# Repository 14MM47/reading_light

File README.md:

# Moon reading light

A clip-on book light: a slim pack clips to the back cover of a book, a ~12 cm plastic-sleeved metal gooseneck rises
from its top, and a 50 mm 3D-printed lithophane moon at the end glows from LEDs in its base. One slide switch turns
it on and off; a main button cycles ten light modes (CRI-97 tunable whites from 2700 K to 5000 K, 6500 K and a 1900 K candle mixed with the RGB LED, red/orange
night lights, green, blue); up/down buttons set brightness; holding the main button for 2 s saves the current
colour and brightness as the power-on default. USB-C charging, 1200 mAh LiPo.

This repo was produced end to end by Claude Code as a test of the full product-design process
(requirements → research → electronics → layout → firmware → mechanical → verification → BOM/ordering).

| What | Where |
|---|---|
| **Everything to build it, in build order** (PCB files, order lists, print files, firmware hex, drawings, PDFs of every instruction and checklist) | [`deliverable/`](deliverable/): start with `00-START-HERE.pdf` |
| How every part fits (exploded and section views) | [`docs/design/fitment/`](docs/design/fitment/) |
| Requirements, architecture, decisions, status | [`PLAN.md`](PLAN.md) |
| PCB fabrication files (Gerbers zip, BOM, pick-and-place, PDFs, STEP) | [`fab/`](fab/) |
| Printed parts, ready to slice (STL + 3MF) and print settings | [`print/`](print/) |
| Farnell order list and other purchases, assembly cost comparison | [`bom/`](bom/) |
| Firmware (PlatformIO) | [`firmware/`](firmware/) |
| KiCad projects and the generator | [`hardware/`](hardware/) |
| Part models (build123d) and the check pipeline | [`cad/`](cad/) |
| Design calculations, optics, thermal, verification reports | [`docs/`](docs/) |
| Step-by-step handoffs for Claude Code in VS Code (ordering, printing, flashing, bring-up) | [`docs/handoffs/`](docs/handoffs/) |

Moon texture: NASA's Scientific Visualization Studio, CGI Moon Kit (LRO LROC / LOLA data, public domain).

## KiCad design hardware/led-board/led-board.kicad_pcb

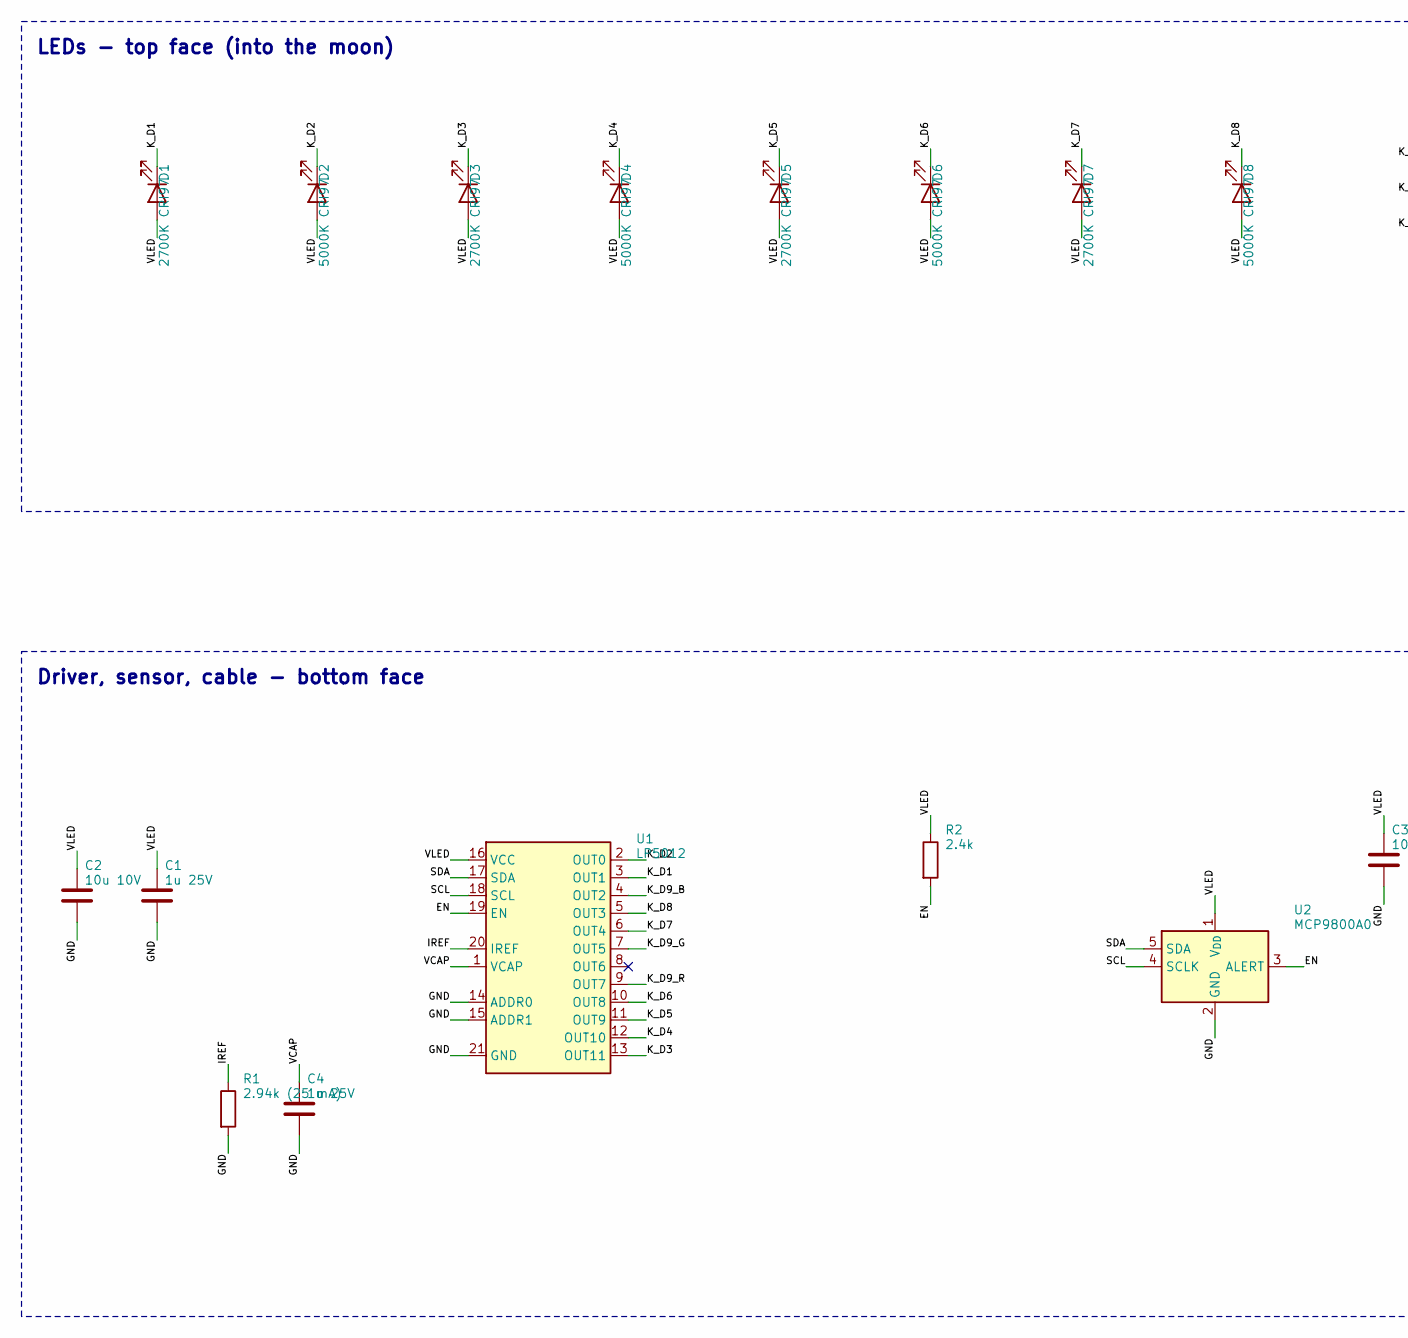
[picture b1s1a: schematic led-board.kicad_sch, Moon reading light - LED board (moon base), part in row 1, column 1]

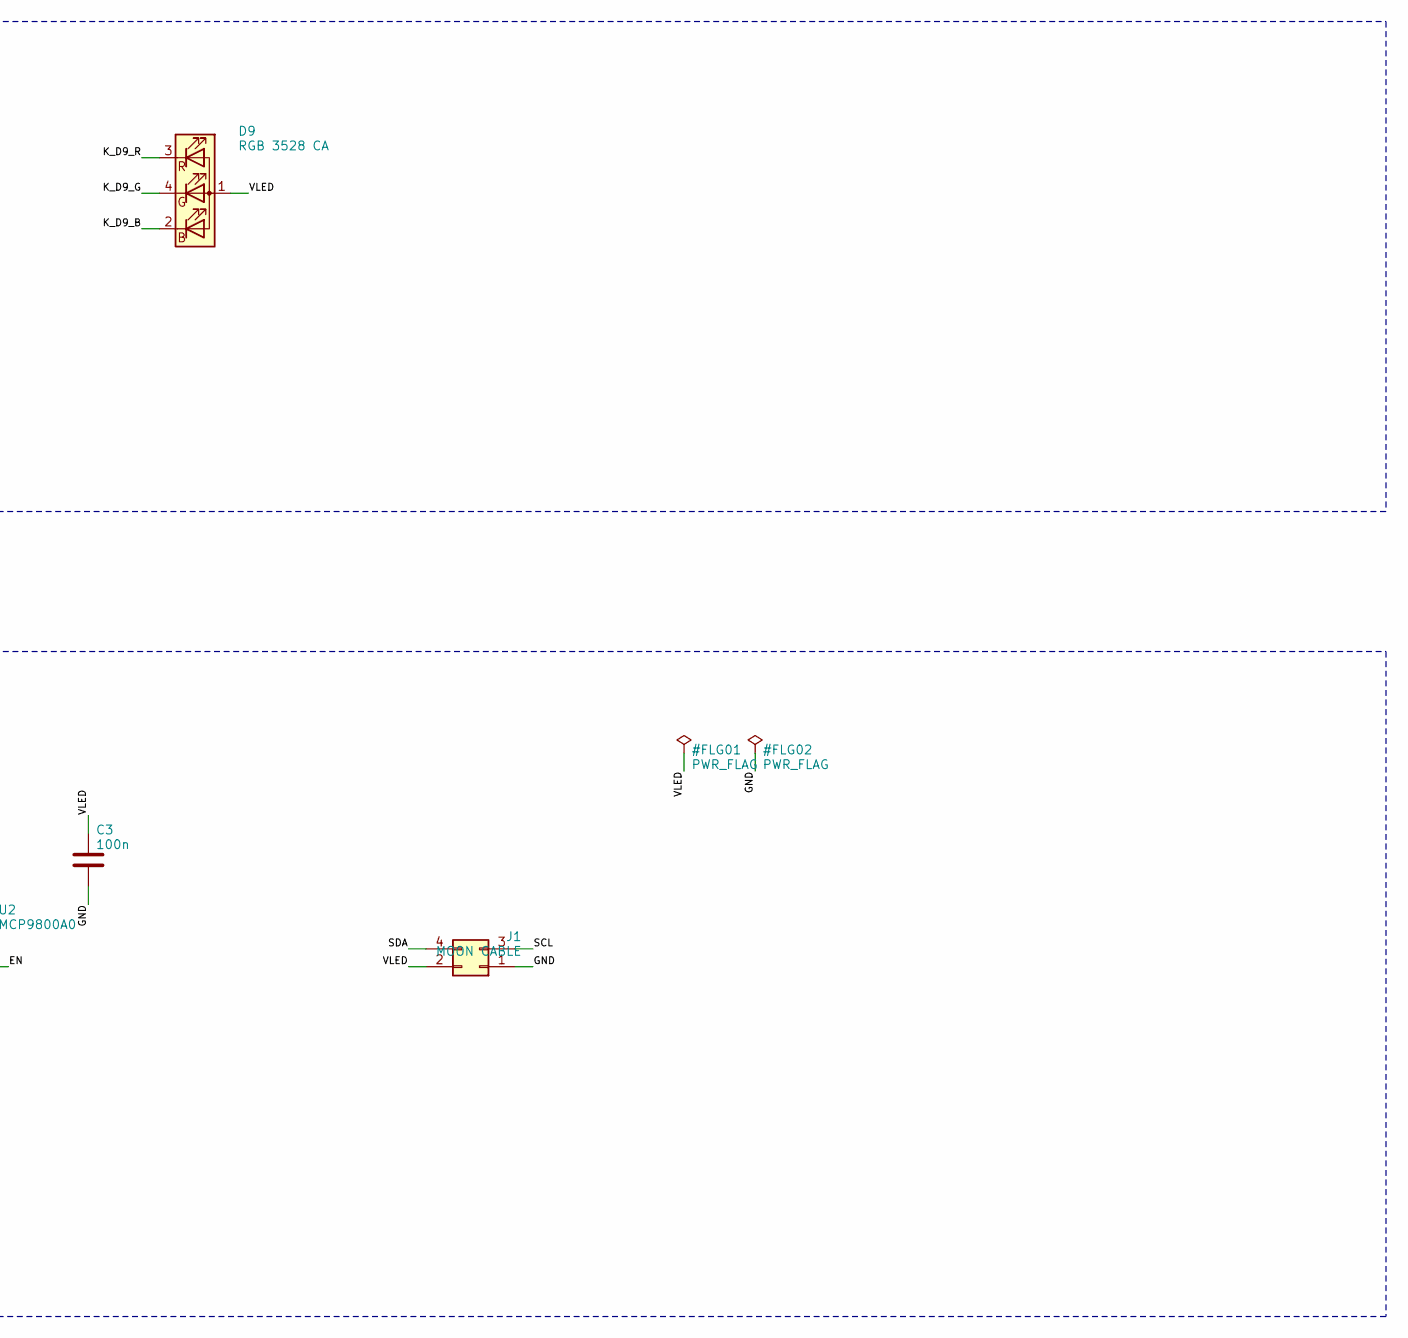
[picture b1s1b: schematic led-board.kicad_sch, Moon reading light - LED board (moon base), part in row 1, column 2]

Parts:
C1, C4: 1u 25V; C_0402_1005Metric; MPN GRM155R61E105KA12D
C2: 10u 10V; C_0603_1608Metric; MPN GRM188R61A106KE69D
C3: 100n; C_0402_1005Metric; MPN GRM155R71C104KA88D
D1, D3, D5, D7: 2700K CRI97; LED_PLCC_2835_Dense; MPN BXEN-27S-11M-3C-00-0-3; Farnell 3498849
D2, D4, D6, D8: 5000K CRI97; LED_PLCC_2835_Dense; MPN BXEN-50S-11M-3C-00-0-3; Farnell 3498853
D9: RGB 3528 CA; LED_RGB_Wuerth-PLCC4_3.2x2.8mm_150141M173100; MPN 150141M173100; Farnell 2322115
J1: MOON CABLE; LED_WirePads_2x02_P1.90mm
R1: 2.94k (25 mA); R_0402_1005Metric; MPN RC0402FR-072K94L
R2: 2.4k; R_0402_1005Metric; MPN RC0402FR-072K4L
U1: LP5012; Texas_RUK0020B_WQFN-20-1EP_3x3mm_P0.4mm_EP1.7x1.7mm; MPN LP5012RUKR
U2: MCP9800A0; SOT-23-5; MPN MCP9800A0T-M/OT; Farnell 1439485

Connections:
/EN: R2.2, U1.19 (EN), U2.3 (ALERT)
/GND: C1.2, C2.2, C3.2, C4.2, J1.1, R1.2, U1.14 (ADDR0), U1.15 (ADDR1), U1.21 (GND), U2.2 (GND)
/IREF: R1.1, U1.20 (IREF)
/K_D1: D1.1 (K), U1.3 (OUT1)
/K_D2: D2.1 (K), U1.2 (OUT0)
/K_D3: D3.1 (K), U1.13 (OUT11)
/K_D4: D4.1 (K), U1.12 (OUT10)
/K_D5: D5.1 (K), U1.11 (OUT9)
/K_D6: D6.1 (K), U1.10 (OUT8)
/K_D7: D7.1 (K), U1.6 (OUT4)
/K_D8: D8.1 (K), U1.5 (OUT3)
/K_D9_B: D9.2 (BK), U1.4 (OUT2)
/K_D9_G: D9.4 (GK), U1.7 (OUT5)
/K_D9_R: D9.3 (RK), U1.9 (OUT7)
/SCL: J1.3, U1.18 (SCL), U2.4 (SCLK)
/SDA: J1.4, U1.17 (SDA), U2.5 (SDA)
/VCAP: C4.1, U1.1 (VCAP)
/VLED: C1.1, C2.1, C3.1, D1.2 (A), D2.2 (A), D3.2 (A), D4.2 (A), D5.2 (A), D6.2 (A), D7.2 (A), D8.2 (A), D9.1 (A), J1.2, R2.1, U1.16 (VCC), U2.1 (V_{DD})

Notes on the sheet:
LEDs - top face (into the moon)
Driver, sensor, cable - bottom face

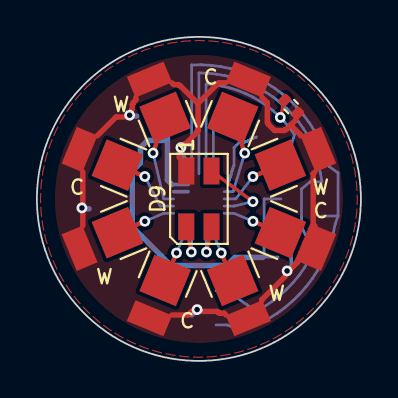
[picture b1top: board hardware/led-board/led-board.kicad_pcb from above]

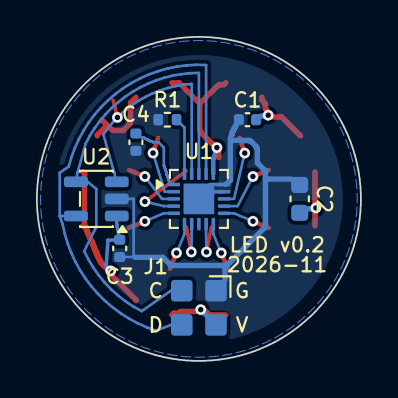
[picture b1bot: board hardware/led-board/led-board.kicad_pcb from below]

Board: 2 copper layers, 18.0 x 18.0 mm, 18 parts (8 on the bottom side), 18 nets.

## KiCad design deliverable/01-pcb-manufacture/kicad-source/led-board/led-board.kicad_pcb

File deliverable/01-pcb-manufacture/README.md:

# 01: PCB manufacture

Two boards: main board rev 0.1, LED board rev 0.2. For each board, upload
**`<board>-v<rev>-gerbers.zip`** to the fab and copy the specs from **`FAB_NOTES.pdf`** (or `.md`) into the order
form. Instructions: `handoff-01-pcb-order.pdf`.

| Board | Size | Stack | Finish / mask | Stencil | Qty |
|---|---|---|---|---|---|
| `main-board/` (in the pack) | 35 × 62 mm | 2 layers, 1.6 mm FR4, 1 oz | HASL lead-free, green / white silk | top, 0.12 mm | 5 |
| `led-board/` (in the moon base) | **Ø 18 mm** round, 0.15/0.15 mm rules | 2 layers, **1.0 mm** FR4, 1 oz | **ENIG, white mask / black silk** | top 0.12 mm **and** bottom **0.10 mm** | 5 |

Files per board:
- `*-gerbers.zip`: Gerber X2 for every layer, plus PTH and NPTH Excellon drill files. **This is the upload.**
- `FAB_NOTES.*`: board spec, special requests, what the remaining DRC warnings mean.
- `*-schematic.pdf`, `*.step`: some fabs ask for these. The STEP lacks 3D models for J1, J2, F1 and the 2835 LEDs;
  re-export it locally before using it for fit checks.
- `optional-assembly-service/`: BOM and placement files for PCBWay or JLCPCB, **only if you choose fab assembly**.
  Main board: bare board plus hand assembly. LED board: fab assembly of the bottom face (U1, U2, R1, C1–C4) is
  recommended, then hand-fit the top (`02-parts-order/assembly-routes-cost-comparison.pdf`).
- `images/`: top and bottom renders for a visual check against the fab's online viewer.

`kicad-source/`: the generated KiCad 9 projects with their project symbol and footprint library, so the
`../lib` paths resolve. PCBWay can take a `.kicad_pcb` directly. These are generated from `hardware/<board>/design.py`;
edit the Python, not these files.

Check results: main-board ERC 0, DRC errors 0,
unconnected 0; led-board ERC 0, DRC errors
0, unconnected 0.

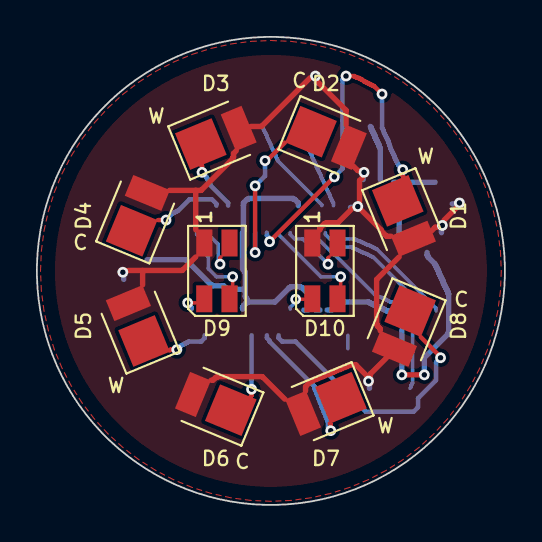
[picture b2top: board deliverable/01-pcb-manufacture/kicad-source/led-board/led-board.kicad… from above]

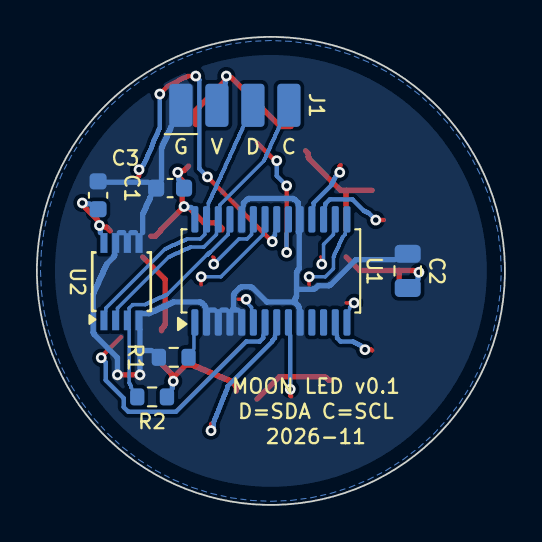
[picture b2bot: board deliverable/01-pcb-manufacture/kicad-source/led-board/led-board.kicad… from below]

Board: 2 copper layers, 26.0 x 26.0 mm, 18 parts (8 on the bottom side), 20 nets.

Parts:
C1, C3: 100n; C_0603_1608Metric
C2: 10u 16V 0805; C_0805_2012Metric
D1, D3, D5, D7: 2700K CRI97; LED_PLCC_2835
D2, D4, D6, D8: 5000K CRI97; LED_PLCC_2835
D9, D10: RGB 3528 CA; LED_RGB_Wuerth-PLCC4_3.2x2.8mm_150141M173100
J1: MOON CABLE; LED_WirePads_1x04_P2.00mm
R1: 750 (25 mA); R_0603_1608Metric
R2: 2.4k; R_0603_1608Metric
U1: TLC59116IPWR; TSSOP-28_4.4x9.7mm_P0.65mm
U2: LM75BDP; TSSOP-8_3x3mm_P0.65mm

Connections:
/GND: C1.2, C2.2, C3.2, J1.1, R1.2, U1.2, U1.3, U1.4, U1.5, U1.10, U1.19, U1.24, U2.4, U2.5, U2.6, U2.7
/K_D1: D1.1, U1.21
/K_D2: D2.1, U1.20
/K_D3: D3.1, U1.18
/K_D4: D4.1, U1.17
/K_D5: D5.1, U1.13
/K_D6: D6.1, U1.9
/K_D7: D7.1, U1.8
/K_D8: D8.1, U1.7
/K_D9_B: D9.2, U1.16
/K_D9_G: D9.4, U1.15
/K_D9_R: D9.3, U1.14
/K_D10_B: D10.2, U1.23
/K_D10_G: D10.4, U1.22
/K_D10_R: D10.3, U1.6
/RESET_N: R2.2, U1.25, U2.3
/REXT: R1.1, U1.1
/SCL: J1.4, U1.26, U2.2
/SDA: J1.3, U1.27, U2.1
/VLED: C1.1, C2.1, C3.1, D1.2, D2.2, D3.2, D4.2, D5.2, D6.2, D7.2, D8.2, D9.1, D10.1, J1.2, R2.1, U1.28, U2.8

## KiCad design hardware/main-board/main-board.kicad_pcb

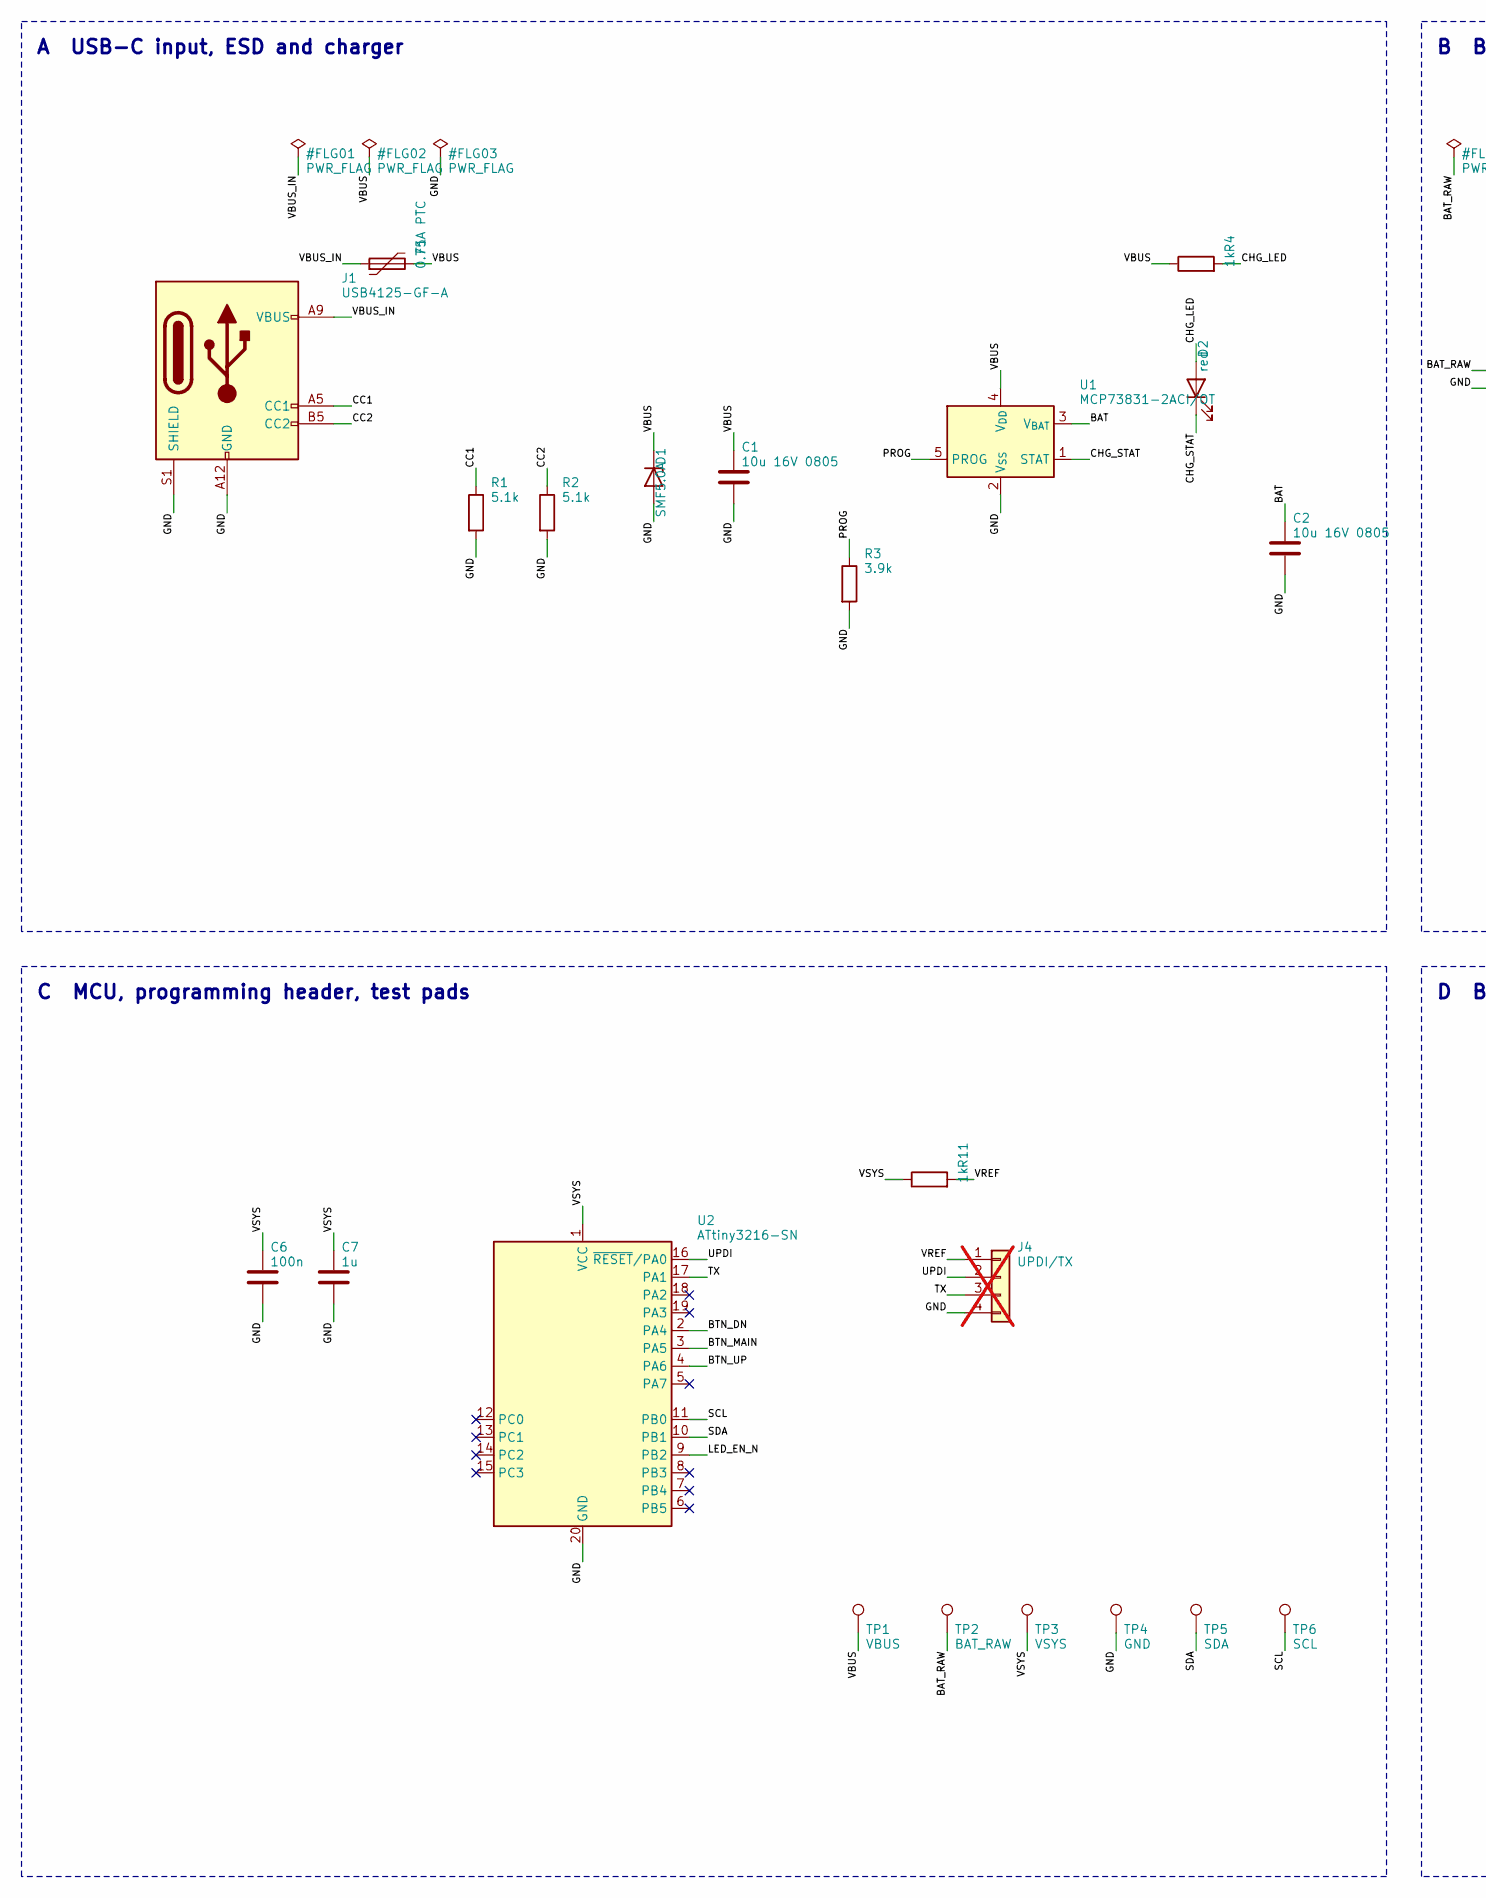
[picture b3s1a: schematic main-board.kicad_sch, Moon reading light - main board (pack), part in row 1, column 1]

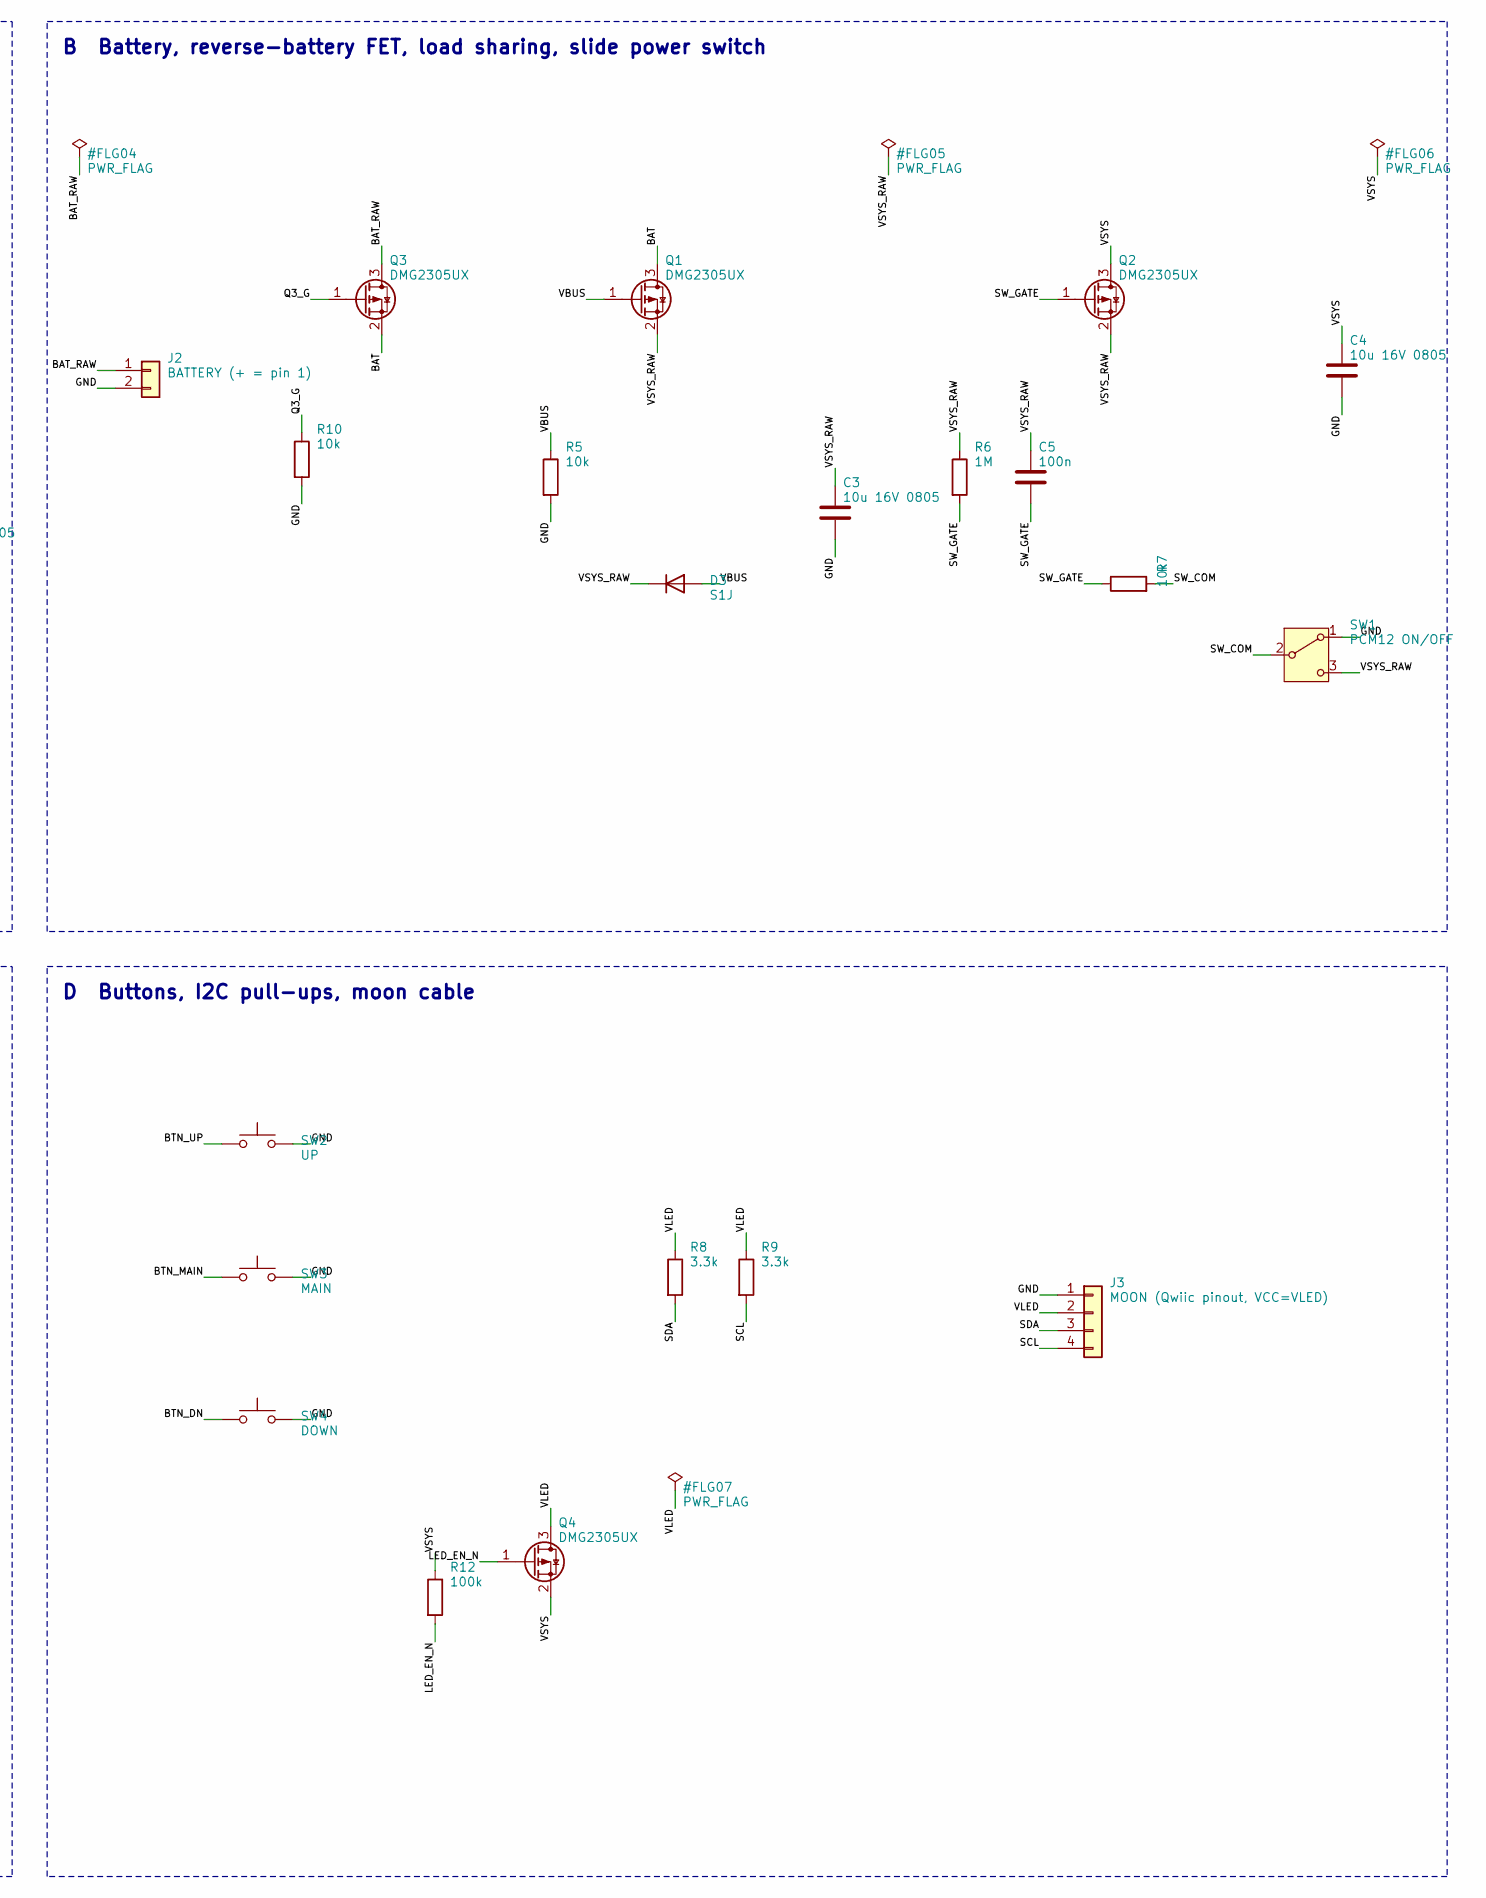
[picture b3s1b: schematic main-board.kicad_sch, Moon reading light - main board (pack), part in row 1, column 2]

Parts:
C1, C2, C3, C4: 10u 16V 0805; C_0805_2012Metric; MPN CL21A106KOQNNNE
C5, C6: 100n; C_0603_1608Metric; MPN MC0603B104K500CT; Farnell 1759122
C7: 1u; C_0603_1608Metric; MPN CL10A105KB8NNNC; Farnell 3013385
D1: SMF5.0A; D_SOD-123F; MPN SMF5.0A; Farnell 2691565
D2: red; LED_0603_1608Metric; MPN APT1608SURCK
D3: S1J; D_SMA; MPN S1J-E3/61T
F1: 0.75A PTC; Fuse_1812_4532Metric; MPN MF-MSMF075-2
J1: USB4125-GF-A; USB_C_Receptacle_GCT_USB4125-xx-x_6P_TopMnt_Horizontal; MPN USB4125-GF-A; Farnell 3648642
J2: BATTERY (+ = pin 1); JST_PH_S2B-PH-SM4-TB_1x02-1MP_P2.00mm_Horizontal; MPN S2B-PH-SM4-TB(LF)(SN); Farnell 9492615
J3: MOON (Qwiic pinout, VCC=VLED); JST_SH_SM04B-SRSS-TB_1x04-1MP_P1.00mm_Horizontal; MPN SM04B-SRSS-TB(LF)(SN); Farnell 1830839
J4: UPDI/TX; PinHeader_1x04_P2.54mm_Vertical; MPN DNP; not fitted
Q1, Q2, Q3, Q4: DMG2305UX; SOT-23; MPN DMG2305UX-7; Farnell 2543533
R1, R2: 5.1k; R_0603_1608Metric; MPN MCWR06X5101FTL
R3: 3.9k; R_0603_1608Metric; MPN MCWR06X3901FTL
R4, R11: 1k; R_0603_1608Metric; MPN MCWR06X1001FTL
R5, R7, R10: 10k; R_0603_1608Metric; MPN MCWR06X1002FTL; Farnell 2447230
R6: 1M; R_0603_1608Metric; MPN MCWR06X1004FTL
R8, R9: 3.3k; R_0603_1608Metric; MPN MCWR06X3301FTL
R12: 100k; R_0603_1608Metric; MPN MCWR06X1003FTL
SW1: PCM12 ON/OFF; SW_SPDT_PCM12; MPN PCM12SMTR; Farnell 9575146
SW2: UP; SW_SPST_PTS645Sx43SMTR92; MPN PTS645SM43SMTR92 LFS; Farnell 3941596
SW3: MAIN; SW_SPST_PTS645Sx43SMTR92; MPN PTS645SM43SMTR92 LFS; Farnell 3941596
SW4: DOWN; SW_SPST_PTS645Sx43SMTR92; MPN PTS645SM43SMTR92 LFS; Farnell 3941596
TP1: VBUS; TestPoint_Pad_D1.5mm
TP2: BAT_RAW; TestPoint_Pad_D1.5mm
TP3: VSYS; TestPoint_Pad_D1.5mm
TP4: GND; TestPoint_Pad_D1.5mm
TP5: SDA; TestPoint_Pad_D1.5mm
TP6: SCL; TestPoint_Pad_D1.5mm
U1: MCP73831-2ACI/OT; SOT-23-5; MPN MCP73831T-2ACI/OT; Farnell 1332158
U2: ATtiny3216-SN; SOIC-20W_7.5x12.8mm_P1.27mm; MPN ATTINY3216-SN; Farnell 3018703

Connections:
/BAT: C2.1, Q1.3 (D), Q3.2 (S), U1.3 (V_{BAT})
/BAT_RAW: J2.1, Q3.3 (D), TP2.1
/BTN_DN: SW4.1, U2.2 (PA4)
/BTN_MAIN: SW3.1, U2.3 (PA5)
/BTN_UP: SW2.1, U2.4 (PA6)
/CC1: J1.A5 (CC1), R1.1
/CC2: J1.B5 (CC2), R2.1
/CHG_LED: D2.2 (A), R4.2
/CHG_STAT: D2.1 (K), U1.1 (STAT)
/GND: C1.2, C2.2, C3.2, C4.2, C6.2, C7.2, D1.2 (A), J1.A12 (GND), J1.B12 (GND), J1.S1 (SHIELD), J2.2, J3.1, J4.4, R1.2, R2.2, R3.2, R5.2, R10.2, SW1.1 (A), SW2.2, SW3.2, SW4.2, TP4.1, U1.2 (V_{SS}), U2.20 (GND)
/LED_EN_N: Q4.1 (G), R12.2, U2.9 (PB2)
/PROG: R3.1, U1.5 (PROG)
/Q3_G: Q3.1 (G), R10.1
/SCL: J3.4, R9.2, TP6.1, U2.11 (PB0)
/SDA: J3.3, R8.2, TP5.1, U2.10 (PB1)
/SW_COM: R7.2, SW1.2 (B)
/SW_GATE: C5.2, Q2.1 (G), R6.2, R7.1
/TX: J4.3, U2.17 (PA1)
/UPDI: J4.2, U2.16 (~RESET/PA0)
/VBUS: C1.1, D1.1 (K), D3.2 (A), F1.2, Q1.1 (G), R4.1, R5.1, TP1.1, U1.4 (V_{DD})
/VBUS_IN: F1.1, J1.A9 (VBUS), J1.B9 (VBUS)
/VLED: J3.2, Q4.3 (D), R8.1, R9.1
/VREF: J4.1, R11.2
/VSYS: C4.1, C6.1, C7.1, Q2.3 (D), Q4.2 (S), R11.1, R12.1, TP3.1, U2.1 (VCC)
/VSYS_RAW: C3.1, C5.1, D3.1 (K), Q1.2 (S), Q2.2 (S), R6.1, SW1.3 (C)

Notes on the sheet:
A USB-C input, ESD and charger
B Battery, reverse-battery FET, load sharing, slide power switch
C MCU, programming header, test pads
D Buttons, I2C pull-ups, moon cable

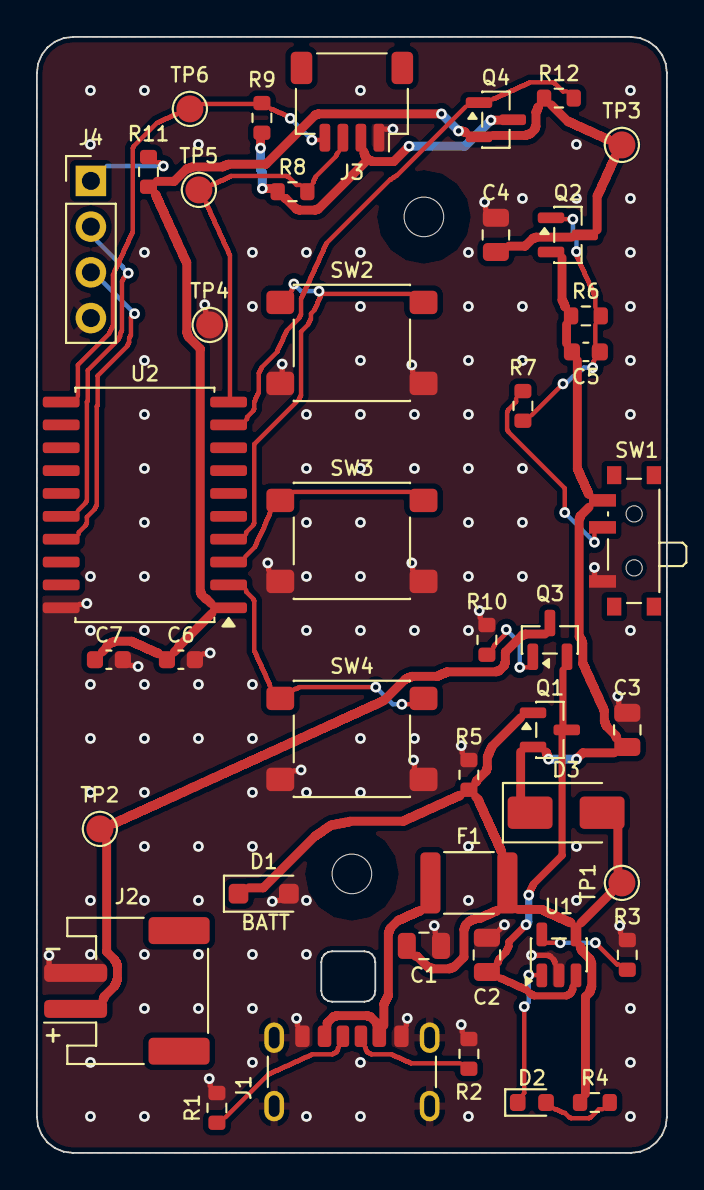
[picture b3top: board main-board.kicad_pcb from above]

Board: 2 copper layers, 35.0 x 62.0 mm, 45 parts (0 on the bottom side), 25 nets.

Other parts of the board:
H1, H2: hole

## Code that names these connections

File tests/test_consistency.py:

"""Cross-domain consistency: firmware <-> netlists <-> design files. Run: python3 -m pytest tests -q
(needs KiCad 9's kicad-cli on PATH and the generated hardware/*/reports/*.net from hardware/build.py)."""
import importlib.util
import re
import subprocess
from pathlib import Path

import pytest

ROOT = Path(__file__).resolve().parents[1]
GROUPS = {"WW": 0, "CW": 1, "R": 2, "G": 3, "B": 4}


def netlist(board):
    path = ROOT / "hardware" / board / "reports" / f"{board}.test.net"
    subprocess.run(["kicad-cli", "sch", "export", "netlist", "--format", "kicadsexpr", "-o", str(path),
                    str(ROOT / "hardware" / board / f"{board}.kicad_sch")], check=True, capture_output=True)
    text = path.read_text()
    path.unlink()
    nets = {}
    for m in re.finditer(r'\(net \(code "\d+"\) \(name "([^"]+)"\)(.*?)\)\s*\)\s*(?=\(net |\)\s*\)\s*$)', text, re.S):
        nodes = re.findall(r'\(node \(ref "([^"]+)"\) \(pin "([^"]+)"\)', m.group(2))
        nets[m.group(1)] = nodes
    return nets


def load_design(board):
    spec = importlib.util.spec_from_file_location(f"{board}_d", ROOT / "hardware" / board / "design.py")
    mod = importlib.util.module_from_spec(spec)
    spec.loader.exec_module(mod)
    return mod


def board_map():
    txt = (ROOT / "firmware" / "include" / "board_map.h").read_text()
    return [int(x) for x in re.search(r"OUT_GROUP\[N_OUT\] = \{([^}]*)\}", txt).group(1).split(",")]


def test_board_map_matches_led_netlist():
    d = load_design("led-board")
    nets = netlist("led-board")
    led_group = {ref: grp for ref, grp, _ in d.WHITE}
    rgb_pin = {"3": "R", "4": "G", "2": "B"}            # Device:LED_ABRG / Wurth 150141M173100
    rgb_refs = {d.RGB_REF}
    expect = [-1] * d.N_OUT
    for out, pin in d.PIN_OF_OUT.items():
        for name, nodes in nets.items():
            if ("U1", pin) in nodes:
                others = [(r, p) for r, p in nodes if r != "U1"]
                for r, p in others:
                    if r in led_group and p == "1":
                        expect[out] = GROUPS[led_group[r]]
                    elif r in rgb_refs and p in rgb_pin:
                        expect[out] = GROUPS[rgb_pin[p]]
    assert board_map() == expect


def test_firmware_pins_match_main_board():
    d = load_design("main-board")
    mcu = next(p for p in d.parts() if p.ref == "U2").pins
    cfg = (ROOT / "firmware" / "include" / "config.h").read_text()
    soic = {"PA4": "2", "PA5": "3", "PA6": "4", "PB2": "9", "PB0": "11", "PB1": "10", "PA1": "17", "PA0": "16"}
    for macro, net in (("PIN_BTN_UP", "BTN_UP"), ("PIN_BTN_MAIN", "BTN_MAIN"), ("PIN_BTN_DN", "BTN_DN"),
                       ("PIN_LED_EN_N", "LED_EN_N")):
        port = re.search(rf"#define {macro}\s+PIN_(P[ABC]\d)", cfg).group(1)
        assert mcu[soic[port]] == net, (macro, port)
    assert mcu["11"] == "SCL" and mcu["10"] == "SDA" and mcu["16"] == "UPDI" and mcu["17"] == "TX"


def test_channel_current_constant_matches_riref():
    d = load_design("led-board")
    riref = next(p for p in d.parts() if p.ref == "R1")
    assert riref.pins["1"] == "IREF"
    v = riref.value.split()[0]
    ohms = float(v[:-1]) * 1000 if v.endswith("k") else float(v)
    i_ma = 105 * 0.7 / ohms * 1000                         # LP5012: ISET = KIREF x VIREF / RIREF (SLVSEH2B)
    core = (ROOT / "firmware" / "lib" / "core" / "lightcore.h").read_text()
    fw = float(re.search(r"#define I_CHANNEL_MA\s+([\d.]+)f", core).group(1))
    assert abs(fw - i_ma) < 0.2, (fw, i_ma)


def test_group_led_counts_match_firmware():
    d = load_design("led-board")
    core = (ROOT / "firmware" / "lib" / "core" / "lightcore.cpp").read_text()
    counts = [int(x) for x in re.search(r"GROUP_LEDS\[G_COUNT\] = \{([^}]*)\}", core).group(1).split(",")]
    ww = sum(1 for w in d.WHITE if w[1] == "WW")
    cw = sum(1 for w in d.WHITE if w[1] == "CW")
    assert counts == [ww, cw, 1, 1, 1]                     # one RGB LED (D9) on LED board v0.2

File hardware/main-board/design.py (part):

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        P("C4", "C_10U", {"1": "VSYS", "2": "GND"}, (395, 70, 0)),
    ]
    # ---- C: MCU, programming header, test points (sheet bottom-left)
    # pins chosen for the layout: PA6/PA5/PA4 run top-to-bottom beside the UP/MAIN/DOWN buttons;
    # debug TX uses USART0's alternate pin PA1 (PORTMUX), next to UPDI and the header
    mcu = {"1": "VSYS", "20": "GND", "16": "UPDI", "17": "TX", "18": None, "19": None,
           "2": "BTN_DN", "3": "BTN_MAIN", "4": "BTN_UP", "5": None,
           "11": "SCL", "10": "SDA", "9": "LED_EN_N", "8": None, "7": None, "6": None,
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        P("C6", "C_100N", {"1": "VSYS", "2": "GND"}, (45, 200, 0)),
        P("C7", "C_1U", {"1": "VSYS", "2": "GND"}, (55, 200, 0)),
        P("R11", "R_1K", {"1": "VSYS", "2": "VREF"}, (140, 185, 90)),
        Part("J4", "Connector_Generic:Conn_01x04", "UPDI/TX", "Connector_PinHeader_2.54mm:PinHeader_1x04_P2.54mm_Vertical",
             {"1": "VREF", "2": "UPDI", "3": "TX", "4": "GND"}, sch=(150, 200, 0),
             fields={"Description": "Programming header: 1 VREF (sense only, 1k - never power the board here), 2 UPDI, 3 TX, 4 GND",
                     "MPN": "DNP", "Farnell": ""}, in_bom=False, dnp=True),
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        P("SW2", "TACT", {"1": "BTN_UP", "2": "GND"}, (240, 180, 0), value="UP"),
        P("SW3", "TACT", {"1": "BTN_MAIN", "2": "GND"}, (240, 200, 0), value="MAIN"),
        P("SW4", "TACT", {"1": "BTN_DN", "2": "GND"}, (240, 220, 0), value="DOWN"),
        # LED-board supply switch: the MCU (PB2 low) powers the LED board; off at reset (R12) and when the battery
        # is empty, so a flat cell is not drained by the LED board (LP5012 ~5 mA; v0.1 TLC59116 ~25 mA, review M2).
        # Pull-ups sit on the switched rail so the unpowered LED board is never back-fed through SDA/SCL.
        P("Q4", "PFET", {"1": "Q4_G", "2": "VSYS", "3": "VLED"}, (280, 240, 0), value="DMG2305UX"),
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        P("R8", "R_3K3", {"1": "VLED", "2": "SDA"}, (300, 200, 0)),
        P("R9", "R_3K3", {"1": "VLED", "2": "SCL"}, (310, 200, 0)),
        P("J3", "JST_SH4", {"1": "GND", "2": "VLED", "3": "SDA", "4": "SCL"}, (360, 205, 0),
          value="MOON (Qwiic pinout, VCC=VLED)"),
    ]
    return v

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BOXES = [(10, 20, 205, 150), (210, 20, 410, 150), (10, 155, 205, 285), (210, 155, 410, 285)]
COMMENTS = [
    "Charge 256 mA (R3 3.9k; total USB draw <= ~0.55 A: use a >= 1 A USB-C charger). Slide switch is the only on/off (Matt).",
    "J3 carries VLED (switched VSYS, not 3.3 V) on the Qwiic pinout: never plug a 3.3 V-only Qwiic device into it.",
    "J2 polarity: + on pin 1 (silk). Q3 blocks a reversed battery; meter every pack before plugging in.",
]

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    "R6": (30.5, 15.5, 0, "F"), "C5": (30.5, 17.5, 0, "F"), "R7": (27.0, 20.5, 90, "F"),
    "SW2": (17.5, 17.0, 0, "F"), "SW3": (17.5, 28.0, 0, "F"), "SW4": (17.5, 39.0, 0, "F"),
    "SW1": (32.85, 28.0, 90, "F"),          # slide switch, knob out of the right edge
    "U2": (6.0, 26.0, 180, "F"),            # pin 1 bottom-right: PA4-6 (buttons) face the buttons, PB0/1 (I2C) at the top
    "C6": (8.0, 34.6, 0, "F"), "C7": (4.0, 34.6, 0, "F"),
    "J4": (3.0, 8.0, 0, "F"),               # UPDI header, top-left (pins run down the left edge)
    "Q3": (28.5, 33.5, 90, "F"), "R10": (25.0, 33.5, 90, "F"),
    "Q1": (28.5, 38.5, 0, "F"), "C3": (32.8, 38.5, 90, "F"),
    "R5": (24.0, 41.0, 90, "F"), "D3": (29.4, 43.1, 0, "F"),
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
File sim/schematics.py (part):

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    d += e.Resistor().at((0, 0)).to((1.8, 0)).label("Rint 0.2 Ω", loc="bottom", fontsize=9)
    d += e.Inductor2(loops=2).at((1.8, 0)).to((3.4, 0)).label("lead 150 nH", loc="bottom", fontsize=9)
    d += e.Line().at((3.4, 0)).to((4.0, 0))
    d += e.Dot().at((4.0, 0)).label("BAT_RAW", loc="top", fontsize=8)
    s3, d3, g3 = _fet(d, 4.0, 0, src_left=False, gate_up=False, label="Q3")
    d += e.Line().at(g3).to((g3[0], -1.2))
    d += e.Resistor().at((g3[0], -1.2)).to((g3[0], -3.0)).label("R10 10k", loc="bottom", fontsize=9)
    d += e.Ground().at((g3[0], -3.0))
    d += e.Line().at(s3).to((6.6, 0))
    d += e.Dot().at((6.17, 0)).label("BAT", loc="bottom", fontsize=8)
    s1, d1, g1 = _fet(d, 6.6, 0, src_left=False, gate_up=True, label="Q1")
    d += e.Line().at(s1).to((9.8, 0))
    d += e.Dot().at((9.0, 0))
    d += e.Label().at((8.7, -0.45)).label("VSYS_RAW", fontsize=8)
    # Q2 + soft-start network below the rail
    s2, d2, g2 = _fet(d, 9.8, 0, src_left=True, gate_up=False, label="")
    d += e.Label().at((10.6, 0.7)).label("Q2", fontsize=10)
    d += e.Line().at(g2).to((g2[0], -2.0))
    d += e.Dot().at((g2[0], -2.0)).label("SW_GATE", loc="right", fontsize=8)
    d += e.Dot().at((9.3, 0))
    d += e.Capacitor().at((9.3, 0)).to((9.3, -2.0)).label("C5 100n\n∥ R6 1M", loc="top", fontsize=9)
    d += e.Line().at((9.3, -2.0)).to((g2[0], -2.0))
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                                                               fontsize=9)
    d += e.Ground().at((g2[0], -5.0))
    d += e.Line().at(d2).to((17.0, 0))
    d += e.Dot().at((12.2, 0)).label("VSYS", loc="top", fontsize=9)
    for x, el, lab in ((12.6, e.Capacitor(), "C4 10µ*"), (14.3, e.Capacitor(), "C7 1µ* ∥\nC6 100n"),
                       (16.5, e.SourceI(), "MCU\n2.5 mA")):
        d += e.Dot().at((x, 0))
        _drop(d, x, 0, el, lab)
    d += e.Arrow().at((17.0, 0)).to((18.2, 0)).label("to Q4 → VLED", loc="top", fontsize=9)
    # ---- USB rail (y = 5)
    Y = 5.0
    d += e.SourceV().at((0, 2.6)).up().length(Y - 2.6).label("USB 4.75-5.25 V", loc="bottom", fontsize=9)
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
def led_path(path):
    d = _d()
    d += e.Dot(open=True).at((-1.6, 0)).label("VSYS", loc="left", fontsize=9)
    d += e.Line().at((-1.6, 0)).to((0, 0))
    s4, d4, g4 = _fet(d, 0, 0, src_left=True, gate_up=True, label="Q4")
    d += e.Line().at((-1.6, 0)).to((-1.6, 2.2))
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    d += e.Line().at(g4).to((g4[0], 2.2))
    d += e.Dot().at((g4[0], 2.2)).label("Q4_G", loc="right", fontsize=8, ofst=(0.1, 0.25))
    d += e.Resistor().at((g4[0], 2.2)).to((g4[0], 4.2)).label("R13 10k", loc="bottom", fontsize=9)
    d += e.Dot(open=True).at((g4[0], 4.2)).label("PB2: VSYS → 0 V", loc="right", fontsize=9)
    d += e.Line().at((g4[0], 2.2)).to((1.4, 2.2))
    d += e.Capacitor().at((1.4, 2.2)).to((3.0, 2.2)).label("C8 100n", loc="top", fontsize=9)
    d += e.Line().at((3.0, 2.2)).to((3.0, 0))
    d += e.Line().at(d4).to((3.4, 0))
    d += e.Dot().at((3.0, 0)).label("VLED", loc="bottom", fontsize=9)
    # cable (both conductors)
    d += e.Resistor().at((3.4, 0)).to((4.9, 0)).label("63 mΩ", loc="top", fontsize=9)
    d += e.Inductor2(loops=2).at((4.9, 0)).to((6.2, 0)).label("75 nH", loc="top", fontsize=9)
    d += e.Label().at((4.8, -0.8)).label("neck cable: J3 + 2 × 200 mm 28 AWG", fontsize=8, color=NOTE)
    d += e.Line().at((6.2, 0)).to((16.4, 0))
    d += e.Label().at((7.0, 0.35)).label("VLED at the LED board", fontsize=8, halign="left")
    yb = -5.0
    cols = ((7.2, e.Capacitor(), "C2 10µ\n0603*"), (9.2, e.Capacitor(), "C1 1µ*\nC3 100n"),
            (11.2, e.SourceI(), "LP5012 VCC\n4-10 mA,\nMCP9800"))
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
def i2c(path):
    d = _d()
    d += e.Vdd().label("VLED 4.2 V")
    d += e.Resistor().down().label("R8 3.3k", loc="right")
    d += (n := e.Dot().label("SDA", loc="right"))
    d += e.Capacitor().down().label("Cbus 60-150 pF", loc="right")
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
